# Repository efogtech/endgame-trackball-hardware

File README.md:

## Endgame Trackball (hardware)

| Revision | Type          | RGB LEDs | Consumption (idle/sleep) | C‑to‑C cable support | Additional exposed pins* | Notes                                      |
|------------|---------------|----------------|-------------|----------------------|--------------------------|--------------------------------------------------|
| rev3       | medium batch  | 🔴           | 🔴 480/130 uA        | ⚠️                    | ❌                        | Doesn't support the new (latest) encoders without a firmware modification. |
| rev4       | large batch   | 🟢           | 🔴 440/110 uA        | ⚠️                    | ❌                        | —                                                |
| rev5       | transitional  | 🟢           | 🟢 110/60 uA         | ✅                    | ❌                        | Restarts when USB power lost.                    |
| rev6       | transitional  | 🟢           | 🟢 95/50 uA          | ✅                    | ⚠️                        | The exposed pins are not very convenient to use. |
| rev7       | ~~final~~     | 🟢           | 🟢 95/50 uA          | ✅                    | ✅                        | The AXP2585 charging IC has got discontinued.    |
| rev8       | transitional  | 🟢           | ?/? uA               | ✅                    | ✅                        | Specifications are to be measured. Has a [hardware issue](https://www.reddit.com/r/efogtech/comments/1vsg4g9/hardware_issue_disclosure/). Can't work without a battery.             |
| rev9       | transitional  | 🟢           | ?/? uA               | ✅                    | ✅                        | Specifications are to be measured. Has the same hardware issue.              |
| rev10      | final         | 🟢           | ?/? uA               | ✅                    | ✅                        | Not in production yet.              |

*Additional 3 GPIOs for arbitrary user modifications. 

#### Why 6 layers?

Because it's cheaper than 4 layers. Yes, seriously.

#### Stackup

JLC06161H-3313

#### Also see

Parent repo: https://github.com/efogtech/endgame-trackball

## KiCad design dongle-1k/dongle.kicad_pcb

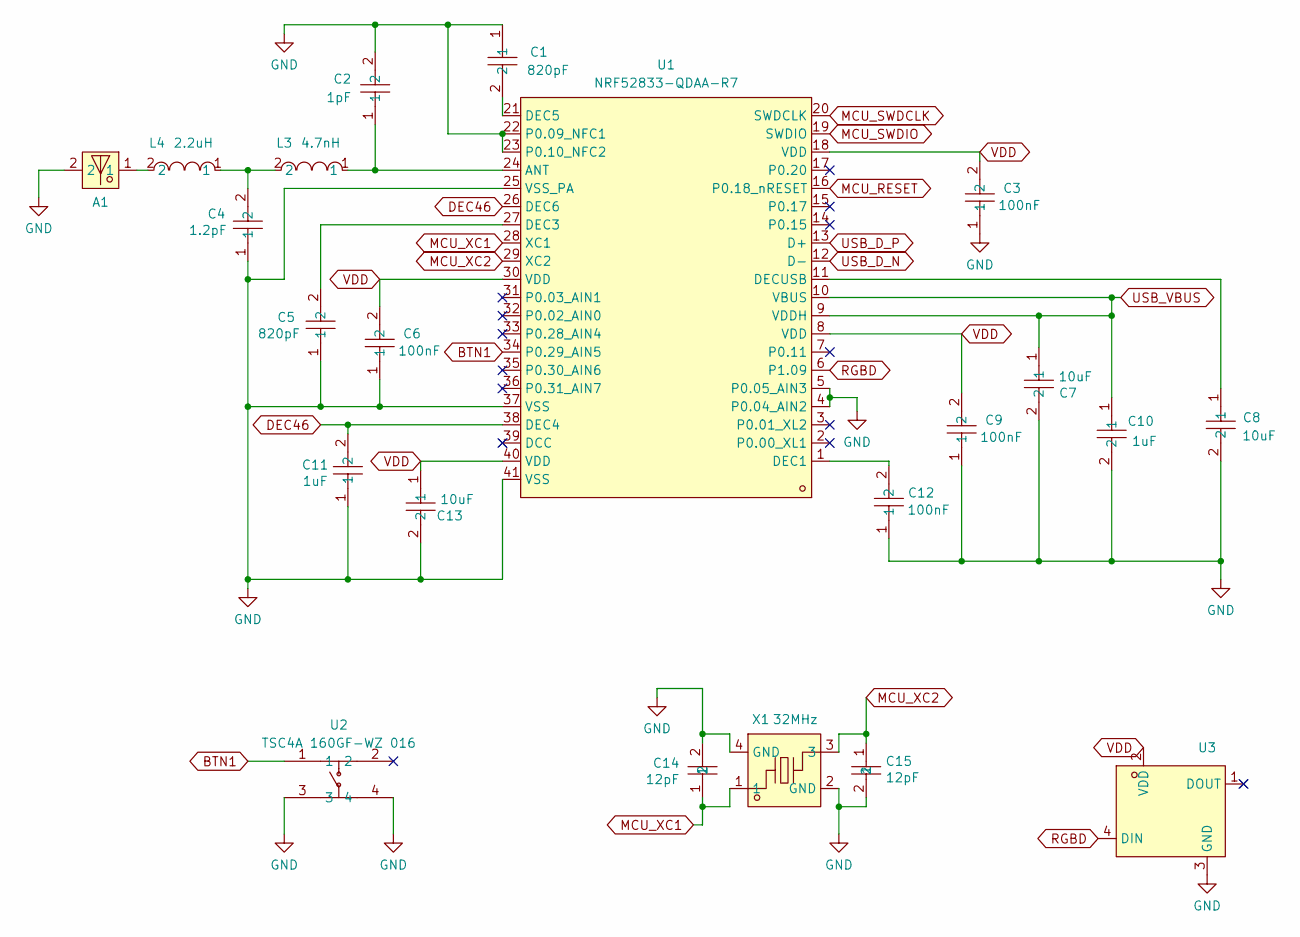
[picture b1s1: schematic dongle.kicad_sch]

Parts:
A1: mifa-2.4ghz-fr4-2.0mm
C1, C5: 0201B821K500NT; C0201; LCSC Part C2836759
C2: 0201CG1R0C250NT; C0201; LCSC Part C301901
C3, C6, C9, C12: CGA0201X5R104K100ET; C0201; LCSC Part C6119757
C4: CGA0201C0G1R2C500ET; C0201; LCSC Part C22374839
C7, C8, C13: CL05A106MP5NUNC_C315248; C0402; LCSC Part C315248
C10, C11: CGA0201X5R105M6R3ET; C0201; LCSC Part C6119749
C14, C15: 0201CG120J500NT; C0201; LCSC Part C50391
L3: LQP03HQ4N7H02D; L0201; LCSC Part C237443
L4: LQP03HQ2N2H02D; L0201; LCSC Part C1329438
U1: NRF52833-QDAA-R7; QFN-40_L5.0-W5.0-P0.40-TL-EP3.6; LCSC Part C3007767
U2: TSC4A 160GF-WZ 016; KEY-SMD_TSC4A; LCSC Part C2906284
U3: XL-1010RGBC-WS2812B; LED-SMD_4P-L1.0-W1.0-TL_XL-1010RGBC-WS2812B; LCSC Part C5349953
X1: XL7EL89CKI-111YLC-32M; CRYSTAL-SMD_4P-L2.0-W1.6-BL; LCSC Part C2965582

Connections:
BTN1: U1.34 (P0.29_AIN5), U2.1
DEC46: C11.2, U1.26 (DEC6), U1.38 (DEC4)
GND: A1.2, C1.1, C2.2, C3.1, C4.1, C5.1, C6.1, C7.2, C8.2, C9.1, C10.2, C11.1, C12.1, C13.2, C14.2, C15.2, U1.4 (P0.04_AIN2), U1.5 (P0.05_AIN3), U1.22 (P0.09_NFC1), U1.23 (P0.10_NFC2), U1.25 (VSS_PA), U1.37 (VSS), U1.41 (VSS), U2.3, U2.4, U3.1 (DOUT), U3.3 (GND), X1.2 (GND), X1.4 (GND)
MCU_RESET: U1.16 (P0.18_nRESET)
MCU_SWDCLK: U1.20 (SWDCLK)
MCU_SWDIO: U1.19 (SWDIO)
MCU_XC1: C14.1, U1.28 (XC1), X1.1
MCU_XC2: C15.1, U1.29 (XC2), X1.3
unnamed: A1.1, L4.2
unnamed: C4.2, L3.2, L4.1
unnamed: C2.1, L3.1, U1.24 (ANT)
unnamed: C12.2, U1.1 (DEC1)
unnamed: C5.2, U1.27 (DEC3)
unnamed: C1.2, U1.21 (DEC5)
unnamed: C8.1, U1.11 (DECUSB)
RGBD: U1.6 (P1.09), U3.4 (DIN)
USB_D_N: U1.12 (D-)
USB_D_P: U1.13 (D+)
USB_VBUS: C7.1, C10.1, U1.9 (VDDH), U1.10 (VBUS)
VDD: C3.2, C6.2, C9.2, C13.1, U1.8 (VDD), U1.18 (VDD), U1.30 (VDD), U1.40 (VDD), U3.2 (VDD)

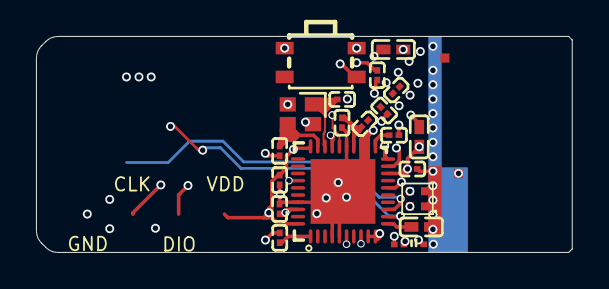
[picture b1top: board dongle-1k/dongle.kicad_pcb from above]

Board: 6 copper layers, 29.8 x 12.0 mm, 22 parts (0 on the bottom side), 15 nets.

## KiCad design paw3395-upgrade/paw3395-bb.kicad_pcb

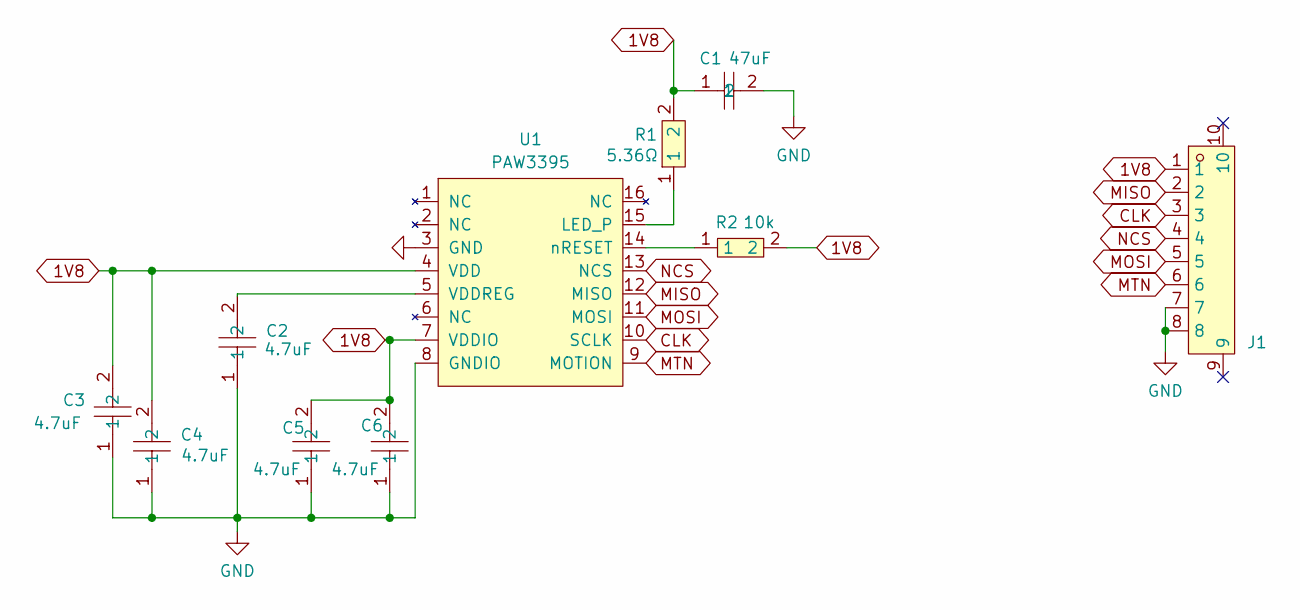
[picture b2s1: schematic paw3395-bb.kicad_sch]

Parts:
C1: GRM188R60J476ME15D; C0603; LCSC Part C140782
C2, C3, C4, C5, C6: GRM035R60J475ME15D; C0201; LCSC Part C335103
J1: AFH34-S08FIA-1H; FPC-SMD_8P-P0.50_JS_AFH34-S08FIA-1H; LCSC Part C5139822
R1: C49254122; R0402; LCSC Part C49254122
R2: RC-01W103JT; R0201; LCSC Part C304504
U1: PAW3395

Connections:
1V8: C1.1, C3.2, C4.2, C5.2, C6.2, J1.1, R1.2, R2.2, U1.4 (VDD), U1.7 (VDDIO)
CLK: J1.3, U1.10 (SCLK)
GND: C1.2, C2.1, C3.1, C4.1, C5.1, C6.1, J1.7, J1.8, U1.3 (GND), U1.8 (GNDIO)
MISO: J1.2, U1.12 (MISO)
MOSI: J1.5, U1.11 (MOSI)
MTN: J1.6, U1.9 (MOTION)
NCS: J1.4, U1.13 (NCS)
unnamed: R1.1, U1.15 (LED_P)
unnamed: C2.2, U1.5 (VDDREG)
unnamed: R2.1, U1.14 (nRESET)

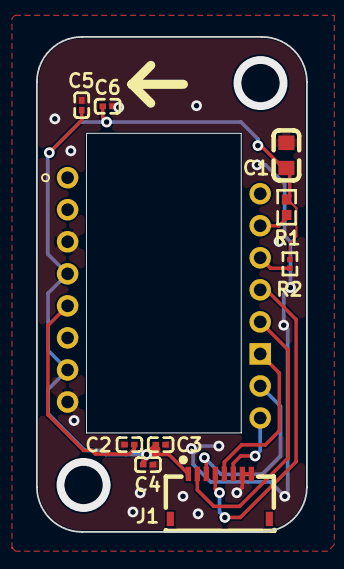
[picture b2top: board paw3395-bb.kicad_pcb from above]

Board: 2 copper layers, 15.0 x 27.5 mm, 10 parts (0 on the bottom side), 10 nets.

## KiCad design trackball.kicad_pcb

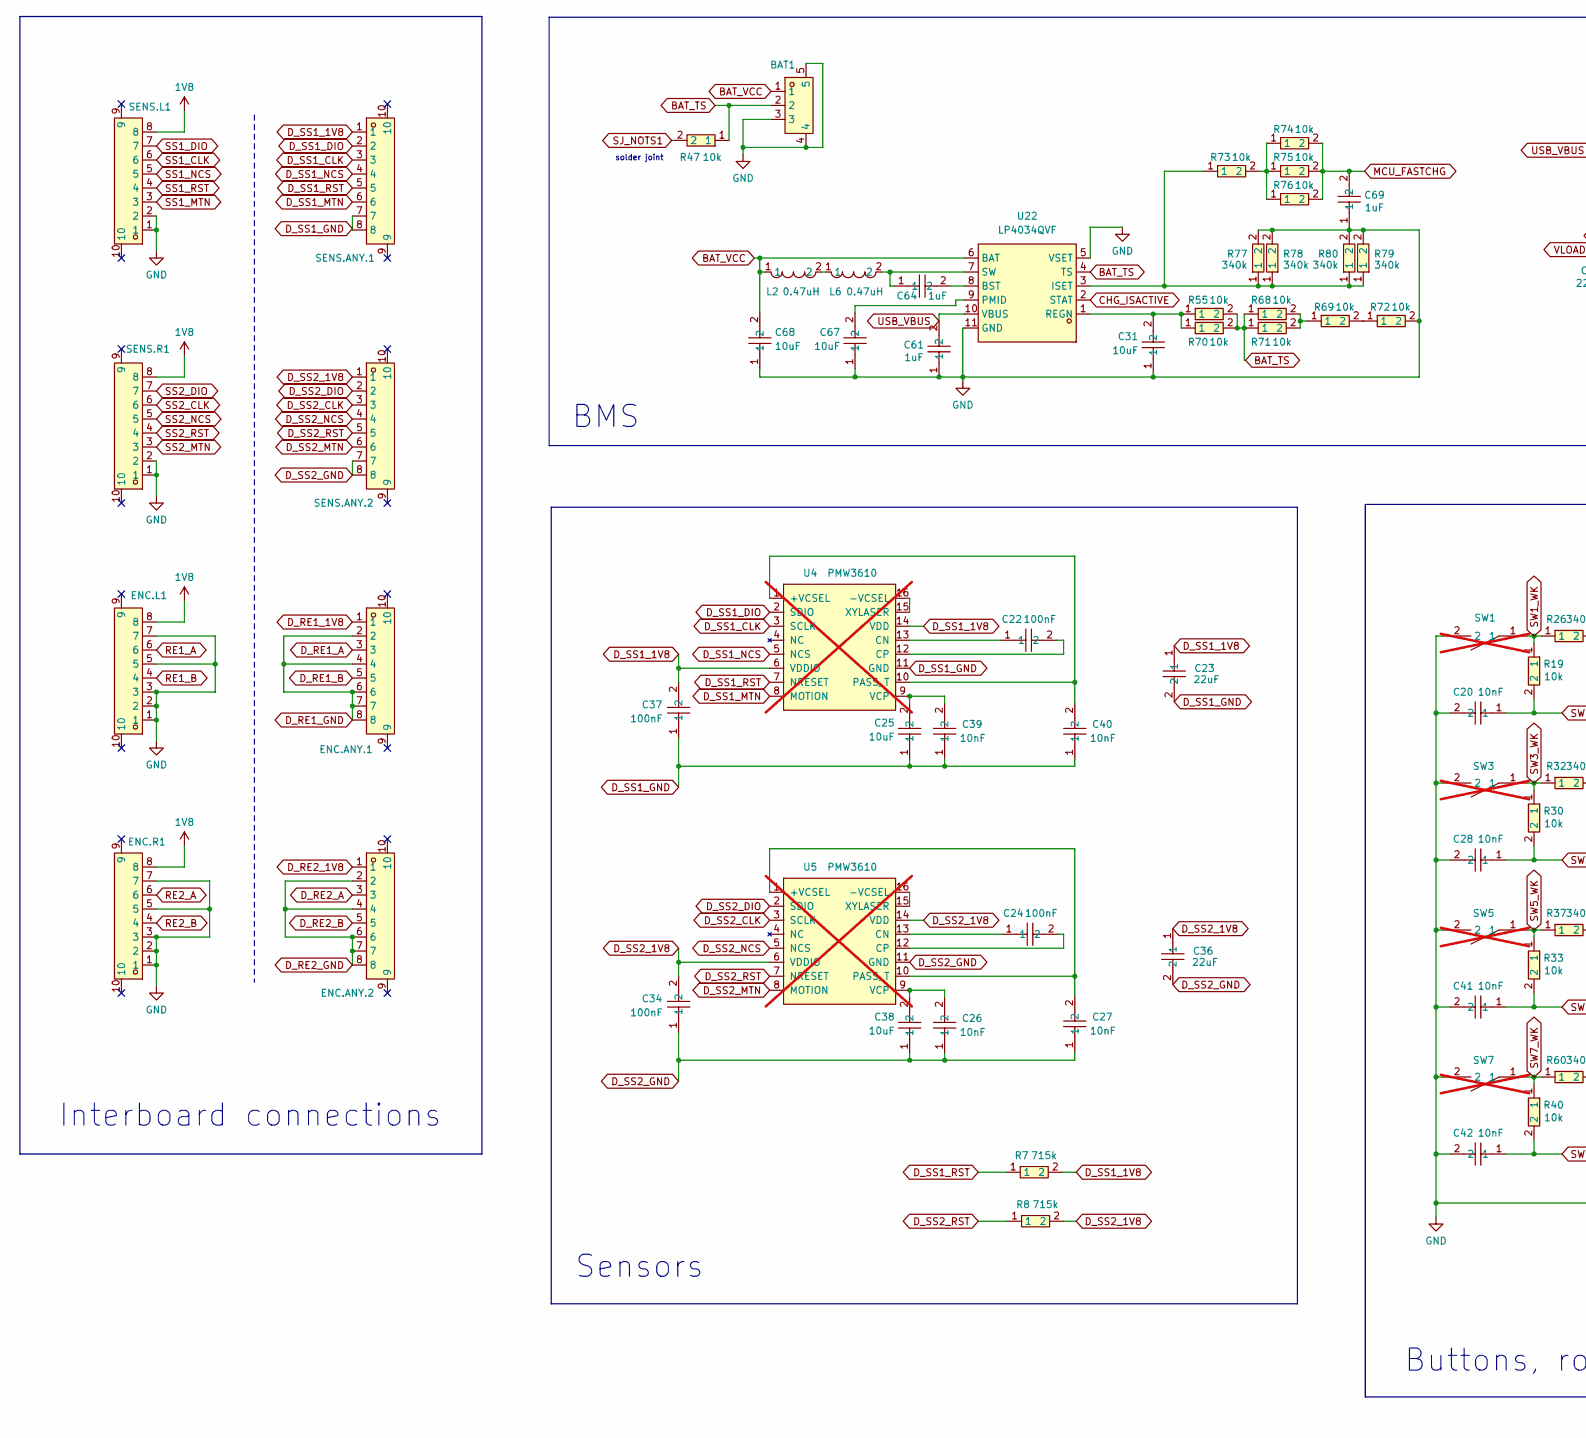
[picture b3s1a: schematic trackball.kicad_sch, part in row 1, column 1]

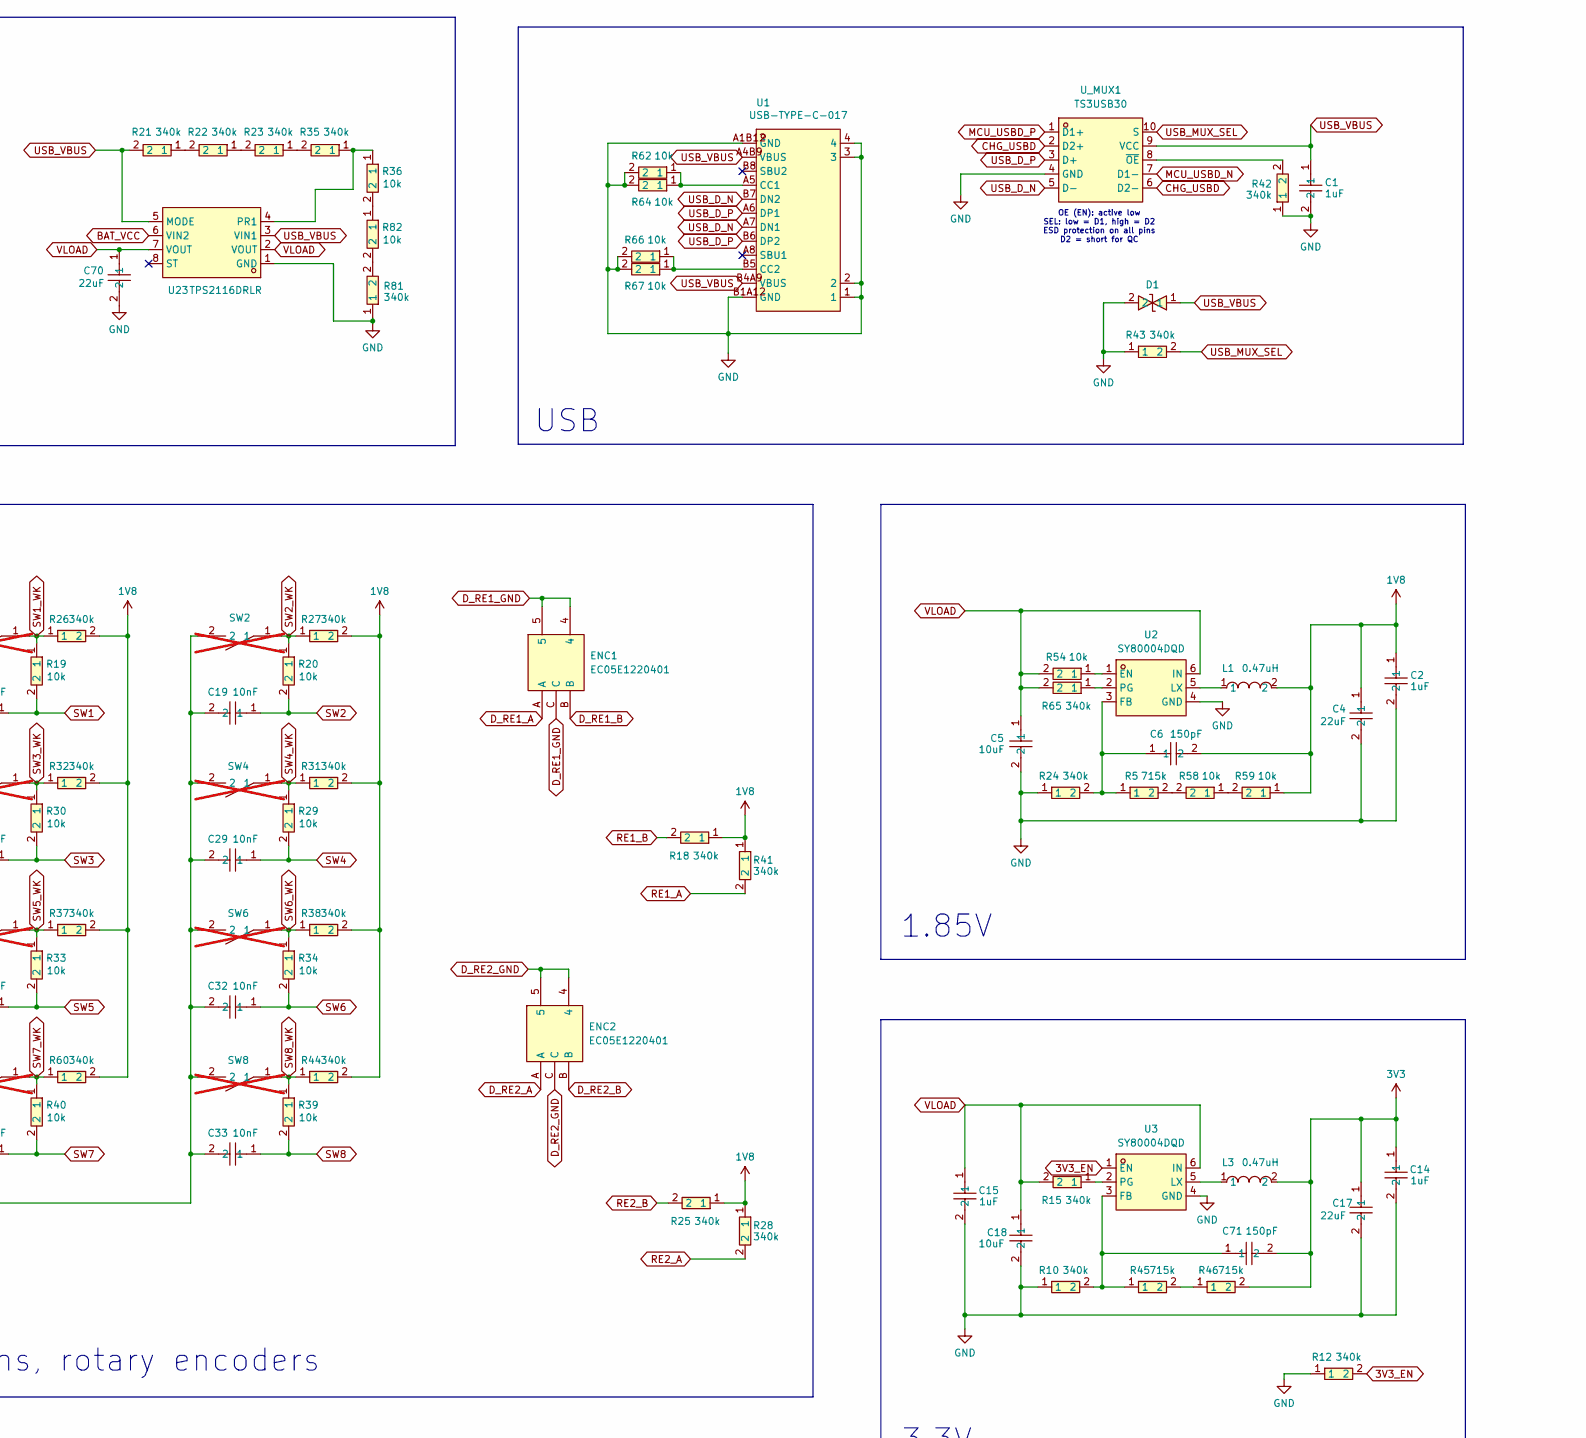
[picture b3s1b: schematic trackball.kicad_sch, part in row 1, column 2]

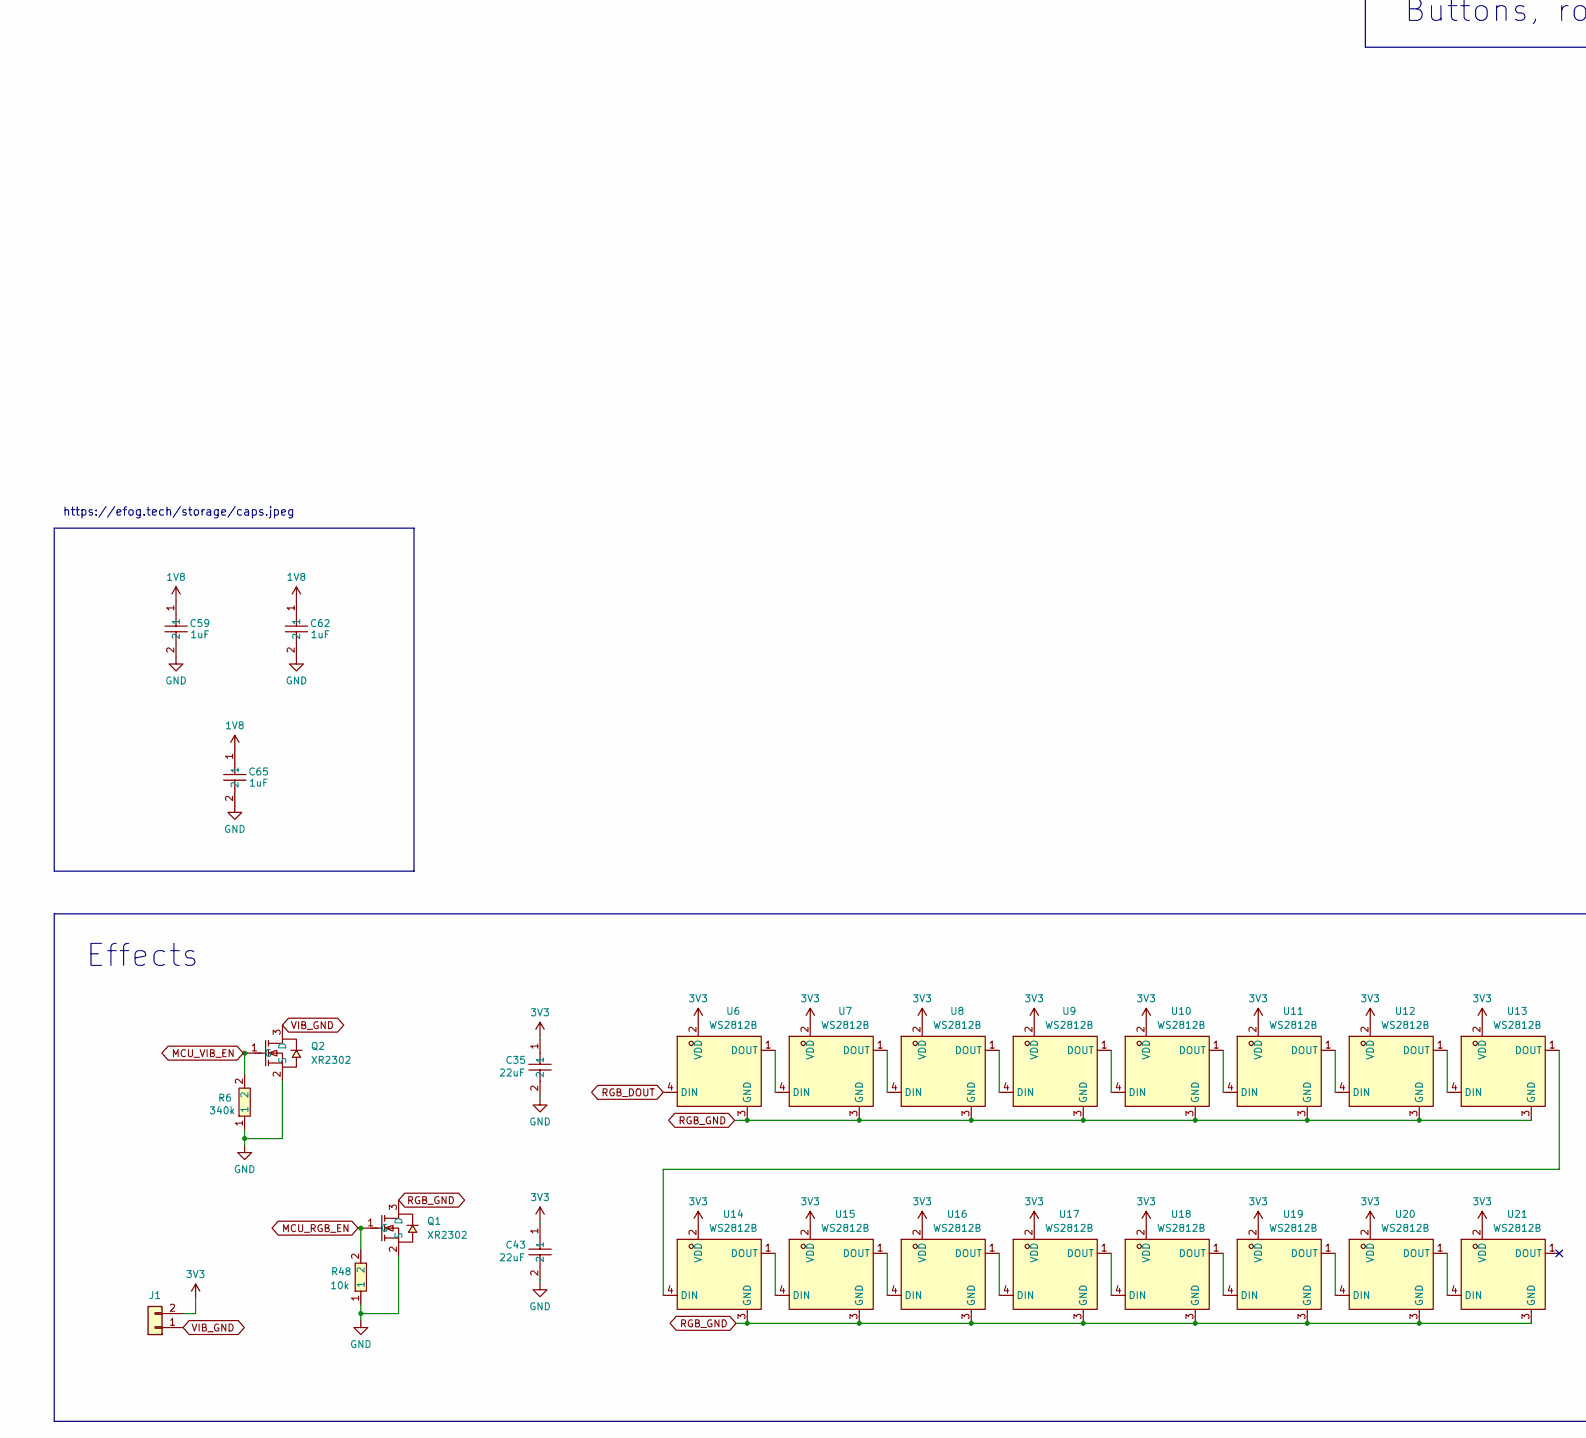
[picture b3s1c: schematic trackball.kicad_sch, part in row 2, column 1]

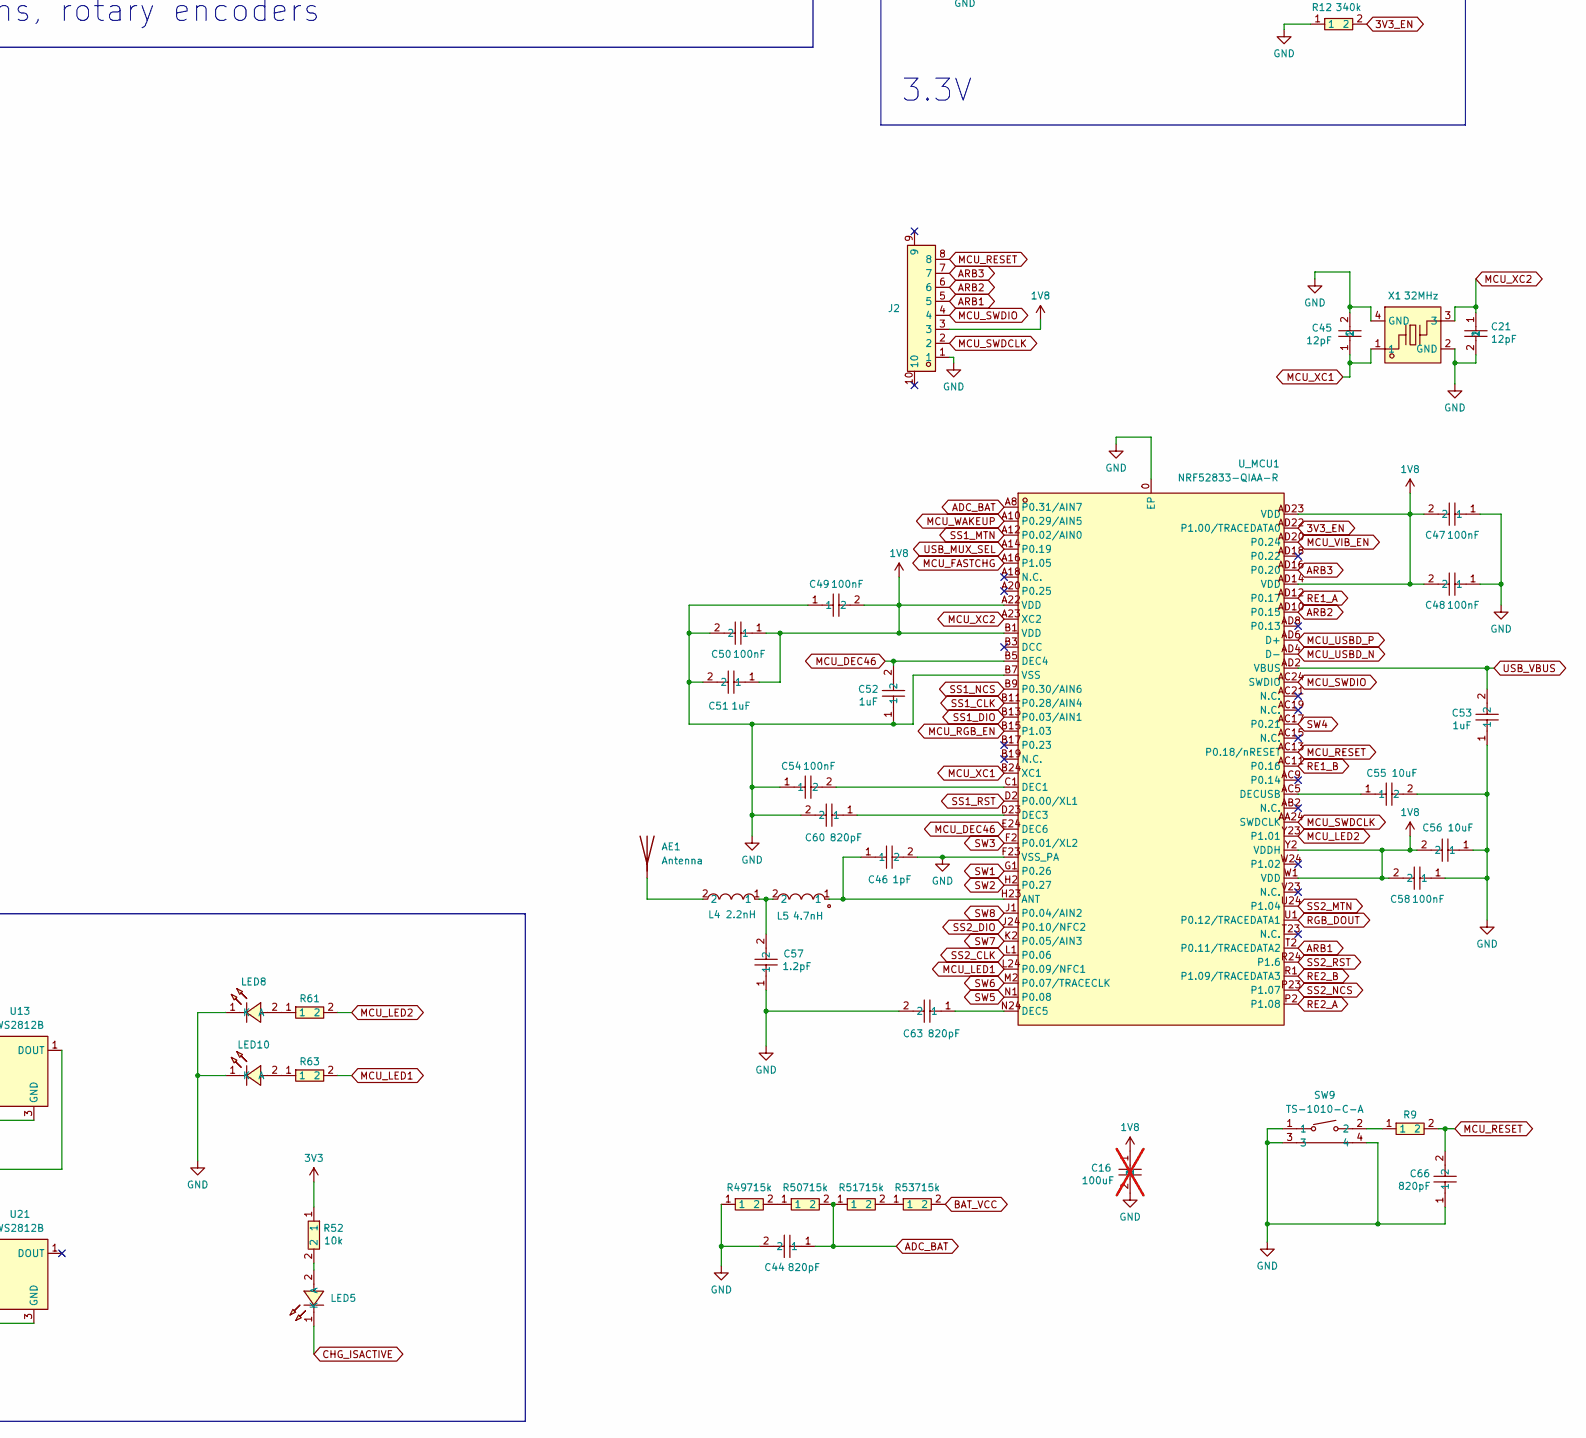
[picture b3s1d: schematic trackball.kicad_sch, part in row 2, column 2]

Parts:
AE1: Antenna; Texas_SWRA117D_2.4GHz_Left
BAT1: HCZZ0032-3; CONN-SMD_HCZZ0032-3; LCSC Part C7433424
C1, C2, C14, C15, C51, C52, C53, C59, C61, C62, C64, C65, C69: CGA0201X5R105M6R3ET; C0201; LCSC Part C6119749
C4, C17, C23, C35, C36, C43, C70: GRM155R60J226ME11D; C0402; LCSC Part C415703
C5, C18, C25, C31, C38, C55, C56, C67, C68: CL05A106MP5NUNC_C315248; C0402; LCSC Part C315248
C6, C71: C0201; LCSC Part C18213206
C16: CL31A107MQHNNNE; C1206; LCSC Part C15008; not fitted
C19, C20, C26, C27, C28, C29, C32, C33, C39, C40, C41, C42: 0201B103K160NT; C0201; LCSC Part C285154
C21, C45: 0201CG120J500NT; C0201; LCSC Part C50391
C22, C24, C34, C37, C47, C48, C49, C50, C54, C58: CGA0201X5R104K100ET; C0201; LCSC Part C6119757
C44, C60, C63, C66: 0201B821K500NT; C0201; LCSC Part C2836759
C46: 0201CG1R0C250NT; C0201; LCSC Part C301901
C57: CGA0201C0G1R2C500ET; C0201; LCSC Part C22374839
D1: 0402ESDA-05N; D0402-BI; LCSC Part C316049
ENC1, ENC2: EC05E1220401; SW-SMD_EC05E1220401; LCSC Part C116648
ENC.ANY.1, ENC.ANY.2, ENC.L1, ENC.R1: AFH34-S08FIA-1H; FPC-SMD_8P-P0.50_JS_AFH34-S08FIA-1H; LCSC Part C5139822
J1: Conn_01x02
J2: AFH34-S08FIA-1H; FPC-SMD_8P-P0.50_JS_AFH34-S08FIA-1H; LCSC Part C5139822
L1, L2, L3, L6: FTC252012SR47MBCA; IND-SMD_L2.5-W2.0; LCSC Part C5832368
L4: LQG15HS2N2S02D; L0402; LCSC Part C86061
L5: LQG15HS4N7S02D; L0402-R-RD; LCSC Part C86065
LED5: XL-1005UGC; LED0402-RD_GREEN; LCSC Part C965793
LED8, LED10: TZ-P2-0402RTIA1-0.45T; LED0402-RD_RED; LCSC Part C779449
Q1, Q2: XR2302; SOT-23-3_L2.9-W1.3-P0.95-LS2.4-BR; LCSC Part C42456447
R5, R7, R8, R45, R46, R49, R50, R51, R53: 715k; R0201; LCSC Part C321023
R6, R10, R12, R15, R18, R21, R22, R23, R24, R25, R26, R27, R28, R31, R32, R35, R37, R38, R41, R42, R43, R44, R60, R65, R77, R78, R79, R80, R81: 0201WMF3403TEE; R0201; LCSC Part C423573
R9, R61, R63: RT0402BRE0750RL; R0402; LCSC Part C853312
R19, R20, R29, R30, R33, R34, R36, R39, R40, R47, R48, R52, R54, R55, R58, R59, R62, R64, R66, R67, R68, R69, R70, R71, R72, R73, R74, R75, R76, R82: 0201WMF1002TEE; R0201; LCSC Part C473048
SENS.ANY.1, SENS.ANY.2, SENS.L1, SENS.R1: AFH34-S08FIA-1H; FPC-SMD_8P-P0.50_JS_AFH34-S08FIA-1H; LCSC Part C5139822
SW1, SW2, SW3, SW4, SW5, SW6, SW7, SW8: HX TC-5608-Y; SW-SMD_TC-5608-Y; LCSC Part C25168853; not fitted
SW9: TS-1010-C-A; KEY-SMD_TX-1010-X-X; LCSC Part C692458
U1: USB-TYPE-C-017; USB-TYPE-C-SMD_C9900008089; LCSC Part C2927037
U2, U3: SY80004DQD; VSON-6_L1.5-W1.5-P0.50-TL; LCSC Part C20617244
U4, U5: PMW3610; not fitted
U6, U7, U8, U9, U10, U11, U12, U13, U14, U15, U16, U17, U18, U19, U20, U21: WS2812B; LED-SMD_4P-L1.0-W1.0-TL_XL-1010RGBC-WS2812B; LCSC Part C5349953
U22: LP4034QVF; DFN-10_L3.0-W3.0-P0.50-BL-EP2.5; MPN LP4034QVF; LCSC Part C42460070
U23: TPS2116DRLR; SOT-583-8_L2.1-W1.6-P0.50-LS1.6-BL; LCSC Part C3235557
U_MCU1: NRF52833-QIAA-R; AQFN-73_L7.0-W7.0-P0.50-BL-EP4.8; LCSC Part C504799
U_MUX1: TS3USB30; UQFN-10_L1.8-W1.4-P0.40-TL; LCSC Part C73880
X1: XL7EL89CKI-111YLC-32M; CRYSTAL-SMD_4P-L2.0-W1.6-BL; LCSC Part C2965582

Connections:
1V8: C2.1, C4.1, C6.2, C16.1, C47.2, C48.2, C49.2, C50.1, C51.1, C56.2, C58.2, C59.1, C62.1, C65.1, ENC.L1.8, ENC.R1.8, J2.3, L1.2, R18.1, R25.1, R26.2, R27.2, R28.1, R31.2, R32.2, R37.2, R38.2, R41.1, R44.2, R59.1, R60.2, SENS.L1.8, SENS.R1.8, U_MCU1.A22 (VDD), U_MCU1.AD14 (VDD), U_MCU1.AD23 (VDD), U_MCU1.B1 (VDD), U_MCU1.W1 (VDD), U_MCU1.Y2 (VDDH); also elsewhere on the board
3V3: C14.1, C17.1, C35.1, C43.1, C71.2, J1.2, L3.2, R46.2, R52.1, U6.2 (VDD), U7.2 (VDD), U8.2 (VDD), U9.2 (VDD), U10.2 (VDD), U11.2 (VDD), U12.2 (VDD), U13.2 (VDD), U14.2 (VDD), U15.2 (VDD), U16.2 (VDD), U17.2 (VDD), U18.2 (VDD), U19.2 (VDD), U20.2 (VDD), U21.2 (VDD)
3V3_EN: R12.2, U3.1 (EN), U_MCU1.AD22 (P1.00/TRACEDATA0)
ADC_BAT: C44.1, R50.2, R51.1, U_MCU1.A8 (P0.31/AIN7)
ARB1: J2.5, U_MCU1.T2 (P0.11/TRACEDATA2)
ARB2: J2.6, U_MCU1.AD10 (P0.15)
ARB3: J2.7, U_MCU1.AD16 (P0.20)
BAT_TS: BAT1.2, R47.1, R55.2, R68.1, R70.2, R71.1, U22.4 (TS)
BAT_VCC: BAT1.1, C68.2, L2.1, R53.2, U22.6 (BAT), U23.6 (VIN2)
CHG_ISACTIVE: LED5.1 (K), U22.2 (STAT)
CHG_USBD: U_MUX1.2 (D2+), U_MUX1.6 (D2-)
D_RE2_A: ENC1.A, ENC.ANY.1.3; also elsewhere on the board
D_RE2_B: ENC1.B, ENC.ANY.1.5; also elsewhere on the board
D_RE2_GND: ENC1.4, ENC1.5, ENC1.C, ENC.ANY.1.2, ENC.ANY.1.4, ENC.ANY.1.6, ENC.ANY.1.7, ENC.ANY.1.8; also elsewhere on the board
D_SS1_1V8: C23.1, C37.2, R7.2, SENS.ANY.1.1, U4.6 (VDDIO), U4.14 (VDD); also elsewhere on the board
D_SS1_CLK: SENS.ANY.1.3, U4.3 (SCLK); also elsewhere on the board
D_SS1_DIO: SENS.ANY.1.2, U4.2 (SDIO); also elsewhere on the board
D_SS1_GND: C23.2, C25.1, C37.1, C39.1, C40.1, SENS.ANY.1.7, SENS.ANY.1.8, U4.11 (GND); also elsewhere on the board
D_SS1_MTN: SENS.ANY.1.6, U4.8 (MOTION); also elsewhere on the board
D_SS1_NCS: SENS.ANY.1.4, U4.5 (NCS); also elsewhere on the board
D_SS1_RST: R7.1, SENS.ANY.1.5, U4.7 (NRESET); also elsewhere on the board
D_SS2_1V8: C34.2, C36.1, R8.2, SENS.ANY.2.1, U5.6 (VDDIO), U5.14 (VDD); also elsewhere on the board
D_SS2_CLK: SENS.ANY.2.3, U5.3 (SCLK); also elsewhere on the board
D_SS2_DIO: SENS.ANY.2.2, U5.2 (SDIO); also elsewhere on the board
D_SS2_GND: C26.1, C27.1, C34.1, C36.2, C38.1, SENS.ANY.2.7, SENS.ANY.2.8, U5.11 (GND); also elsewhere on the board
D_SS2_MTN: SENS.ANY.2.6, U5.8 (MOTION); also elsewhere on the board
D_SS2_NCS: SENS.ANY.2.4, U5.5 (NCS); also elsewhere on the board
D_SS2_RST: R8.1, SENS.ANY.2.5, U5.7 (NRESET); also elsewhere on the board
GND: BAT1.3, BAT1.4, BAT1.5, C1.2, C2.2, C4.2, C5.2, C14.2, C15.2, C16.2, C17.2, C18.2, C19.2, C20.2, C21.2, C28.2, C29.2, C31.1, C32.2, C33.2, C35.2, C41.2, C42.2, C43.2, C44.2, C45.2, C46.2, C47.1, C48.1, C49.1, C50.2, C51.2, C52.1, C53.1, C54.1, C55.2, C56.1, C57.1, C58.1, C59.2, C60.2, C61.1, C62.2, C63.2, C65.2, C66.1, C67.1, C68.1, C69.1, C70.2, D1.2, ENC.L1.1, ENC.L1.2, ENC.L1.3, ENC.L1.5, ENC.L1.7, ENC.R1.1, ENC.R1.2, ENC.R1.3, ENC.R1.5, ENC.R1.7, J2.1, LED8.1 (K), LED10.1 (K), Q1.2 (S), Q2.2 (S), R6.1, R10.1, R12.1, R24.1, R42.1, R43.1, R48.1, R49.1, R62.2, R64.2, R66.2, R67.2, R72.2, R77.2, R78.2, R79.2, R80.2, R81.1, SENS.L1.1, SENS.L1.2, SENS.R1.1, SENS.R1.2, SW1.2, SW2.2, SW3.2, SW4.2, SW5.2, SW6.2, SW7.2, SW8.2, SW9.1, SW9.3, SW9.4, U1.1, U1.2, U1.3, U1.4, U1.A1B12 (GND), U1.B1A12 (GND), U2.4 (GND), U3.4 (GND), U22.5 (VSET), U22.11 (GND), U23.1 (GND), U_MCU1.0 (EP), U_MCU1.B7 (VSS), U_MCU1.F23 (VSS_PA), U_MUX1.4 (GND), X1.2 (GND), X1.4 (GND); also elsewhere on the board
MCU_DEC46: C52.2, U_MCU1.B5 (DEC4), U_MCU1.E24 (DEC6)
MCU_FASTCHG: C69.2, R74.2, R75.2, R76.2, U_MCU1.A16 (P1.05)
MCU_LED1: R63.2, U_MCU1.L24 (P0.09/NFC1)
MCU_LED2: R61.2, U_MCU1.Y23 (P1.01)
MCU_RESET: C66.2, J2.8, R9.2, U_MCU1.AC13 (P0.18/nRESET)
MCU_RGB_EN: Q1.1 (G), R48.2, U_MCU1.B15 (P1.03)
MCU_SWDCLK: J2.2, U_MCU1.AA24 (SWDCLK)
MCU_SWDIO: J2.4, U_MCU1.AC24 (SWDIO)
MCU_USBD_N: U_MCU1.AD4 (D-), U_MUX1.7 (D1-)
MCU_USBD_P: U_MCU1.AD6 (D+), U_MUX1.1 (D1+)
MCU_VIB_EN: Q2.1 (G), R6.2, U_MCU1.AD20 (P0.24)
MCU_WAKEUP: U_MCU1.A10 (P0.29/AIN5); also elsewhere on the board
MCU_XC1: C45.1, U_MCU1.B24 (XC1), X1.1
MCU_XC2: C21.1, U_MCU1.A23 (XC2), X1.3
unnamed: AE1.1 (A_1), L4.2
unnamed: C57.2, L4.1, L5.2
unnamed: ENC2.4, ENC2.5, ENC2.C, ENC.ANY.2.2, ENC.ANY.2.4, ENC.ANY.2.6, ENC.ANY.2.7, ENC.ANY.2.8
unnamed: ENC2.A, ENC.ANY.2.3
unnamed: ENC2.B, ENC.ANY.2.5
unnamed: L2.2, L6.1
unnamed: LED5.2 (A), R52.2
unnamed: LED8.2 (A), R61.1
unnamed: LED10.2 (A), R63.1
unnamed: R5.2, R58.2
unnamed: R9.1, SW9.2
unnamed: R21.1, R22.2
unnamed: R22.1, R23.2
unnamed: R23.1, R35.2
unnamed: R36.2, R82.1
unnamed: R45.2, R46.1
unnamed: R49.2, R50.1
unnamed: R51.2, R53.1
unnamed: R58.1, R59.2
unnamed: R68.2, R69.1, R71.2
unnamed: R69.2, R72.1
unnamed: R73.2, R74.1, R75.1, R76.1
unnamed: R81.2, R82.2
unnamed: R62.1, R64.1, U1.A5 (CC1)
unnamed: R66.1, R67.1, U1.B5 (CC2)
unnamed: R54.1, U2.1 (EN)
unnamed: C6.1, R5.1, R24.2, U2.3 (FB)
unnamed: L1.1, U2.5 (LX)
unnamed: R65.1, U2.2 (PG)
unnamed: C71.1, R10.2, R45.1, U3.3 (FB)
unnamed: L3.1, U3.5 (LX)
unnamed: R15.1, U3.2 (PG)
unnamed: C40.2, U4.1 (+VCSEL), U4.10 (PASS_T)
unnamed: U4.15 (XYLASER), U4.16 (-VCSEL)
unnamed: C22.1, U4.13 (CN)
unnamed: C22.2, U4.12 (CP)
unnamed: C25.2, C39.2, U4.9 (VCP)
unnamed: C27.2, U5.1 (+VCSEL), U5.10 (PASS_T)
unnamed: U5.15 (XYLASER), U5.16 (-VCSEL)
unnamed: C24.1, U5.13 (CN)
unnamed: C24.2, U5.12 (CP)
unnamed: C26.2, C38.2, U5.9 (VCP)
unnamed: U6.1 (DOUT), U7.4 (DIN)
unnamed: U7.1 (DOUT), U8.4 (DIN)
unnamed: U8.1 (DOUT), U9.4 (DIN)
unnamed: U9.1 (DOUT), U10.4 (DIN)
unnamed: U10.1 (DOUT), U11.4 (DIN)
unnamed: U11.1 (DOUT), U12.4 (DIN)
unnamed: U12.1 (DOUT), U13.4 (DIN)
unnamed: U13.1 (DOUT), U14.4 (DIN)
unnamed: U14.1 (DOUT), U15.4 (DIN)
unnamed: U15.1 (DOUT), U16.4 (DIN)
unnamed: U16.1 (DOUT), U17.4 (DIN)
unnamed: U17.1 (DOUT), U18.4 (DIN)
unnamed: U18.1 (DOUT), U19.4 (DIN)
unnamed: U19.1 (DOUT), U20.4 (DIN)
unnamed: U20.1 (DOUT), U21.4 (DIN)
unnamed: C64.2, U22.8 (BST)
unnamed: R73.1, R77.1, R78.1, R79.1, R80.1, U22.3 (ISET)
unnamed: C67.2, U22.9 (PMID)
unnamed: C31.2, R55.1, R70.1, U22.1 (REGN)
unnamed: C64.1, L6.2, U22.7 (SW)
unnamed: R35.1, R36.1, U23.4 (PR1)
unnamed: C46.1, L5.1, U_MCU1.H23 (ANT)
unnamed: C54.2, U_MCU1.C1 (DEC1)
unnamed: C60.1, U_MCU1.D23 (DEC3)
unnamed: C63.1, U_MCU1.N24 (DEC5)
unnamed: C55.1, U_MCU1.AC5 (DECUSB)
unnamed: R42.2, U_MUX1.8 (~OE)
RE1_A: ENC.L1.6, R41.2, U_MCU1.AD12 (P0.17); also elsewhere on the board
RE1_B: ENC.L1.4, R18.2, U_MCU1.AC11 (P0.16); also elsewhere on the board
RE2_A: ENC.R1.6, R28.2, U_MCU1.P2 (P1.08); also elsewhere on the board
RE2_B: ENC.R1.4, R25.2, U_MCU1.R1 (P1.09/TRACEDATA3); also elsewhere on the board
RGB_DOUT: U6.4 (DIN), U_MCU1.U1 (P0.12/TRACEDATA1)
RGB_GND: Q1.3 (D), U6.3 (GND), U7.3 (GND), U8.3 (GND), U9.3 (GND), U10.3 (GND), U11.3 (GND), U12.3 (GND), U13.3 (GND), U14.3 (GND), U15.3 (GND), U16.3 (GND), U17.3 (GND), U18.3 (GND), U19.3 (GND), U20.3 (GND), U21.3 (GND)
SJ_NOTS1: R47.2
SS1_CLK: SENS.L1.6, U_MCU1.B11 (P0.28/AIN4); also elsewhere on the board
SS1_DIO: SENS.L1.7, U_MCU1.B13 (P0.03/AIN1); also elsewhere on the board
SS1_MTN: SENS.L1.3, U_MCU1.A12 (P0.02/AIN0); also elsewhere on the board
SS1_NCS: SENS.L1.5, U_MCU1.B9 (P0.30/AIN6); also elsewhere on the board
SS1_RST: SENS.L1.4, U_MCU1.D2 (P0.00/XL1); also elsewhere on the board
SS2_CLK: SENS.R1.6, U_MCU1.L1 (P0.06); also elsewhere on the board
SS2_DIO: SENS.R1.7, U_MCU1.J24 (P0.10/NFC2); also elsewhere on the board
SS2_MTN: SENS.R1.3, U_MCU1.U24 (P1.04); also elsewhere on the board
SS2_NCS: SENS.R1.5, U_MCU1.P23 (P1.07); also elsewhere on the board
SS2_RST: SENS.R1.4, U_MCU1.R24 (P1.6); also elsewhere on the board
SW1: C20.1, R19.2, U_MCU1.G1 (P0.26)
SW1_WK: R19.1, R26.1, SW1.1; also elsewhere on the board
SW2: C19.1, R20.2, U_MCU1.H2 (P0.27)
SW2_WK: R20.1, R27.1, SW2.1; also elsewhere on the board
SW3: C28.1, R30.2, U_MCU1.F2 (P0.01/XL2)
SW3_WK: R30.1, R32.1, SW3.1; also elsewhere on the board
SW4: C29.1, R29.2, U_MCU1.AC17 (P0.21)
SW4_WK: R29.1, R31.1, SW4.1; also elsewhere on the board
SW5: C41.1, R33.2, U_MCU1.N1 (P0.08)
SW5_WK: R33.1, R37.1, SW5.1; also elsewhere on the board
SW6: C32.1, R34.2, U_MCU1.M2 (P0.07/TRACECLK)
SW6_WK: R34.1, R38.1, SW6.1; also elsewhere on the board
SW7: C42.1, R40.2, U_MCU1.K2 (P0.05/AIN3)
SW7_WK: R40.1, R60.1, SW7.1; also elsewhere on the board
SW8: C33.1, R39.2, U_MCU1.J1 (P0.04/AIN2)
SW8_WK: R39.1, R44.1, SW8.1; also elsewhere on the board
USB_D_N: U1.A7 (DN1), U1.B7 (DN2), U_MUX1.5 (D-)
USB_D_P: U1.A6 (DP1), U1.B6 (DP2), U_MUX1.3 (D+)
USB_MUX_SEL: R43.2, U_MCU1.A14 (P0.19), U_MUX1.10 (S)
USB_VBUS: C1.1, C53.2, C61.2, D1.1, R21.2, U1.A4B9 (VBUS), U1.B4A9 (VBUS), U22.10 (VBUS), U23.3 (VIN1), U23.5 (MODE), U_MCU1.AD2 (VBUS), U_MUX1.9 (VCC)
VIB_GND: J1.1, Q2.3 (D)
VLOAD: C5.1, C15.1, C18.1, C70.1, R15.2, R54.2, R65.2, U2.6 (IN), U3.6 (IN), U23.2 (VOUT), U23.7 (VOUT)

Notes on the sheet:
Effects
Interboard connections
Buttons, rotary encoders
BMS
USB
https://efog.tech/storage/caps.jpeg
3.3V
Sensors
solder joint
1.85V
OE (EN): active low SEL: low = D1, high = D2 ESD protection on all pins D2 = short for QC
